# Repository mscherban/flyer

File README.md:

# flyer
This is my drone project where I am attempting the flight controls from a BeagleBone Black Wireless.

## More Info
* PWM and IMU interface drives are done by me and use Linux Sysfs.
* Made a quick PCB to connect motors, power, and IMU to BBB connection headers.
* I communicate with the drone over WiFi with SSH.

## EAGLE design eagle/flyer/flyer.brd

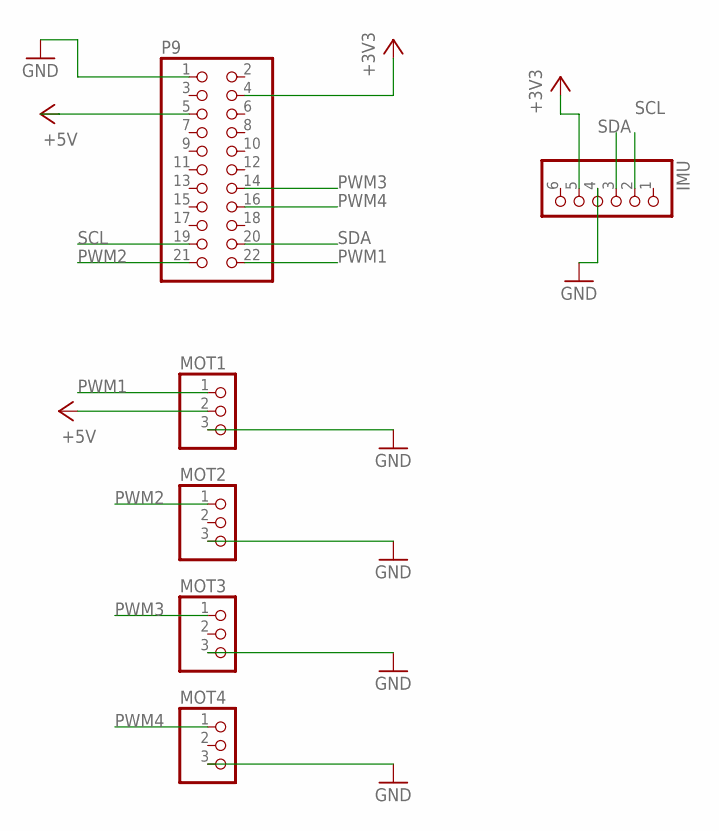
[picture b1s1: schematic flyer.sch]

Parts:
IMU: PINHD-1X6; 1X06
MOT1, MOT2, MOT3, MOT4: PINHD-1X3; 1X03
P9: PINHD-2X11; 2X11

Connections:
+3V3: IMU.5, P9.4
+5V: MOT1.2, P9.5
GND: IMU.4, MOT1.3, MOT2.3, MOT3.3, MOT4.3, P9.1
PWM1: MOT1.1, P9.22
PWM2: MOT2.1, P9.21
PWM3: MOT3.1, P9.14
PWM4: MOT4.1, P9.16
SCL: IMU.2, P9.19
SDA: IMU.3, P9.20

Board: 2 copper layers, 6 parts (0 on the bottom side), 9 nets, no tracks yet.

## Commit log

2019-05-14 add initial files: Pwm driver and main
2019-05-23 add IMU base support
2019-05-23 add an executable that will kill the pwms in a pinch
2019-05-28 use result of read/write to remove compilation error. moved the pwm instance struct array to the pwm file
2019-05-28 IMU driver doesnt covert anymore. also fixed an error message I put in there by mistake
2019-06-04 Added calibration program
    Just added a small calibration program that will set the PWM to whatever
    level I want to set it at.
    I also tested the brushless motor with this and it works.
2019-06-18 Testing out the motors
    Update to the calibration test program to have better control over the motors.
    I tested out increasing the speed till it lifted off.
2019-06-18 Add beginnings for PID
    Added the start for each motor PID control
2019-06-19 Added comments
2019-06-19 Finished adding PID
    But it does not work very well, still many adjustments and tuning necessary.
2019-06-19 Add supporting files
    Added a picture of the drone + eagle files
2019-06-20 Condensed threads
    There is now only 2 threads:
    1. Reading the keyboard input
    2. Reading IMU, stability, and motor control
2019-06-27 Switch from float to integer IMU calculations
    Switched the floating point IMU calculations to integers for speed and higher
    resolution of orientation.
2019-06-28 Add some CSV formatted debug printing
2019-07-01 Fix derivative being subtracted rather than added
2019-07-01 Added some alpha filtering on inputs and error
    This is to smooth out the sampling and resist sudden changes in speed.
